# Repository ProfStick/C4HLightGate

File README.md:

# C4HLightGate
Light Gates and peripherals for timing show jumping rounds
Based on Adafruit Feather & Arduino IDE

This program is free software: you can redistribute it and/or modify it under the terms of the GNU General Public License as published by the Free Software Foundation, either version 3 of the License, or any later version.

This program is distributed in the hope that it will be useful, but WITHOUT ANY WARRANTY; without even the implied warranty of MERCHANTABILITY or FITNESS FOR A PARTICULAR PURPOSE.  See the GNU General Public License for more details.

You should have received a copy of the GNU General Public License along with this program.  If not, see <https://www.gnu.org/licenses/gpl.txt>.

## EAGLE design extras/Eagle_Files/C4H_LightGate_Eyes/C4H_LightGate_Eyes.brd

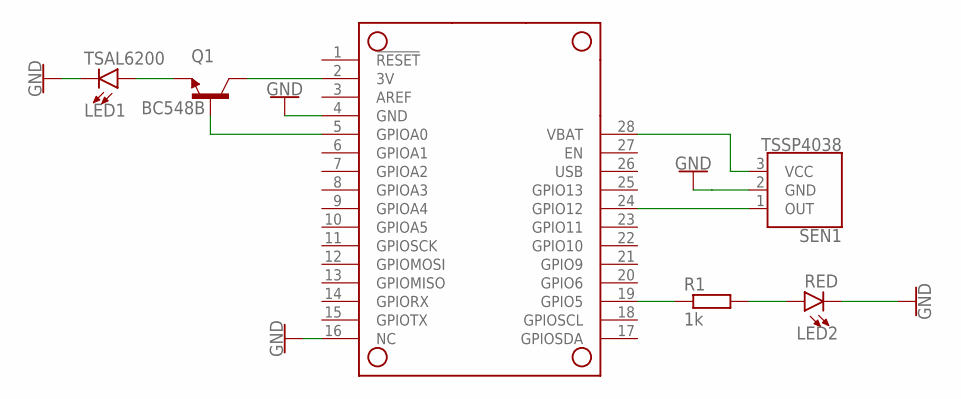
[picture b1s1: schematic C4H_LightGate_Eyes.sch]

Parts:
LED1: TSAL6200; LED5MM
LED2: RED; LED5MM
MS1: FEATHERWING
Q1: BC548B; TO92-EBC
R1: 1k; 0207/7
SEN1: TSSP4038; TSSP40

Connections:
3V: MS1.2 (3V), Q1.C
GND: LED1.K (C), LED2.K (C), MS1.4 (GND), MS1.16 (NC), SEN1.2 (GND)
unnamed: LED1.A, Q1.E
unnamed: MS1.5 (GPIOA0), Q1.B
unnamed: MS1.19 (GPIO5), R1.1
unnamed: LED2.A, R1.2
unnamed: MS1.24 (GPIO12), SEN1.1 (OUT)
VBAT: MS1.28 (VBAT), SEN1.3 (VCC)

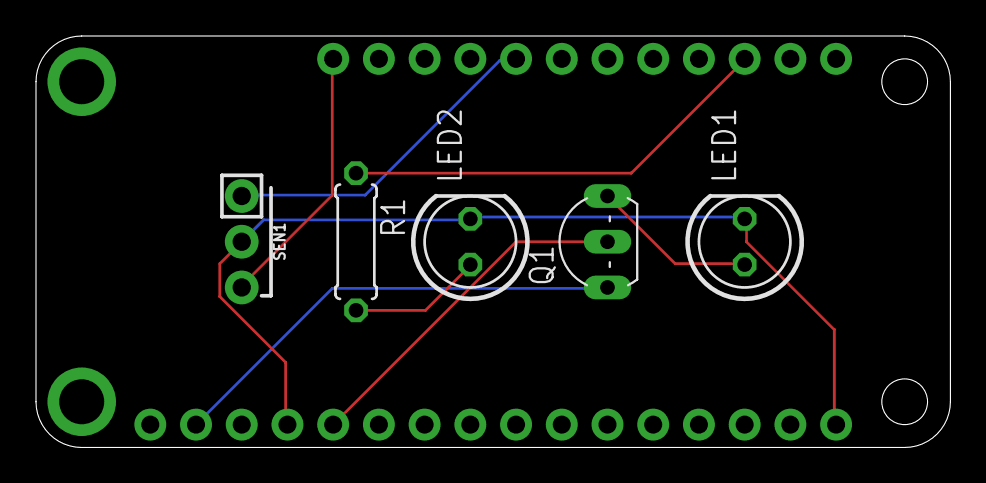
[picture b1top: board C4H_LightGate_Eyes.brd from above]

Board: 2 copper layers, 50.8 x 22.9 mm, 6 parts (0 on the bottom side), 8 nets.

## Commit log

2017-04-17 :space_invader: Added .gitattributes & .gitignore files
2017-04-17 Template for arduino sketches
2017-04-17 Light Gate Send Unit sketch
2018-08-21 updated
    added templates and removed old files including old templates and fritzing files
2018-08-26 added battery check
    added initial battery check method
2018-08-26 file structure reorgainsed
    reorganised in line with Arduino IDE 1.5: Library specification
2018-08-26 added properties metadata
2018-08-26 added license
    added details of GNU GPL license 3

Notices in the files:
parts and their libraries:
SparkFun-PowerSymbols: Licensing: Creative Commons ShareAlike 4.0 International - https://creativecommons.org/licenses/by-sa/4.0
